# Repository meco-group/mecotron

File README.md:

# mecotron

This repository gathers software and hardware details on mobile platforms that were recently designed in support of an introductory control course.

Through dedicated assignments, students are guided to implement and validate all parts of the course on a setup, ranging from basic time-domain system identification, over root locus analysis and loop shaping PID design, to state feedback, state estimation and Kalman filtering.

The designed platforms are flexible, allowing for numerous extensions and variations; cheap, allowing for a large pool of setups from which the students can borrow platforms to take home; and of sufficient quality, allowing the students to get maximal insight in the course material.

The platforms are furthermore easy to set up and administer using the supporting material.

*These set-ups were presented at the demonstrator sessions at the 20th IFAC World Congress (Toulouse, 2017); see [the accompanying paper](https://www.sciencedirect.com/science/article/pii/S240589631732325X) and the video below.*

<p align="center">

</p>

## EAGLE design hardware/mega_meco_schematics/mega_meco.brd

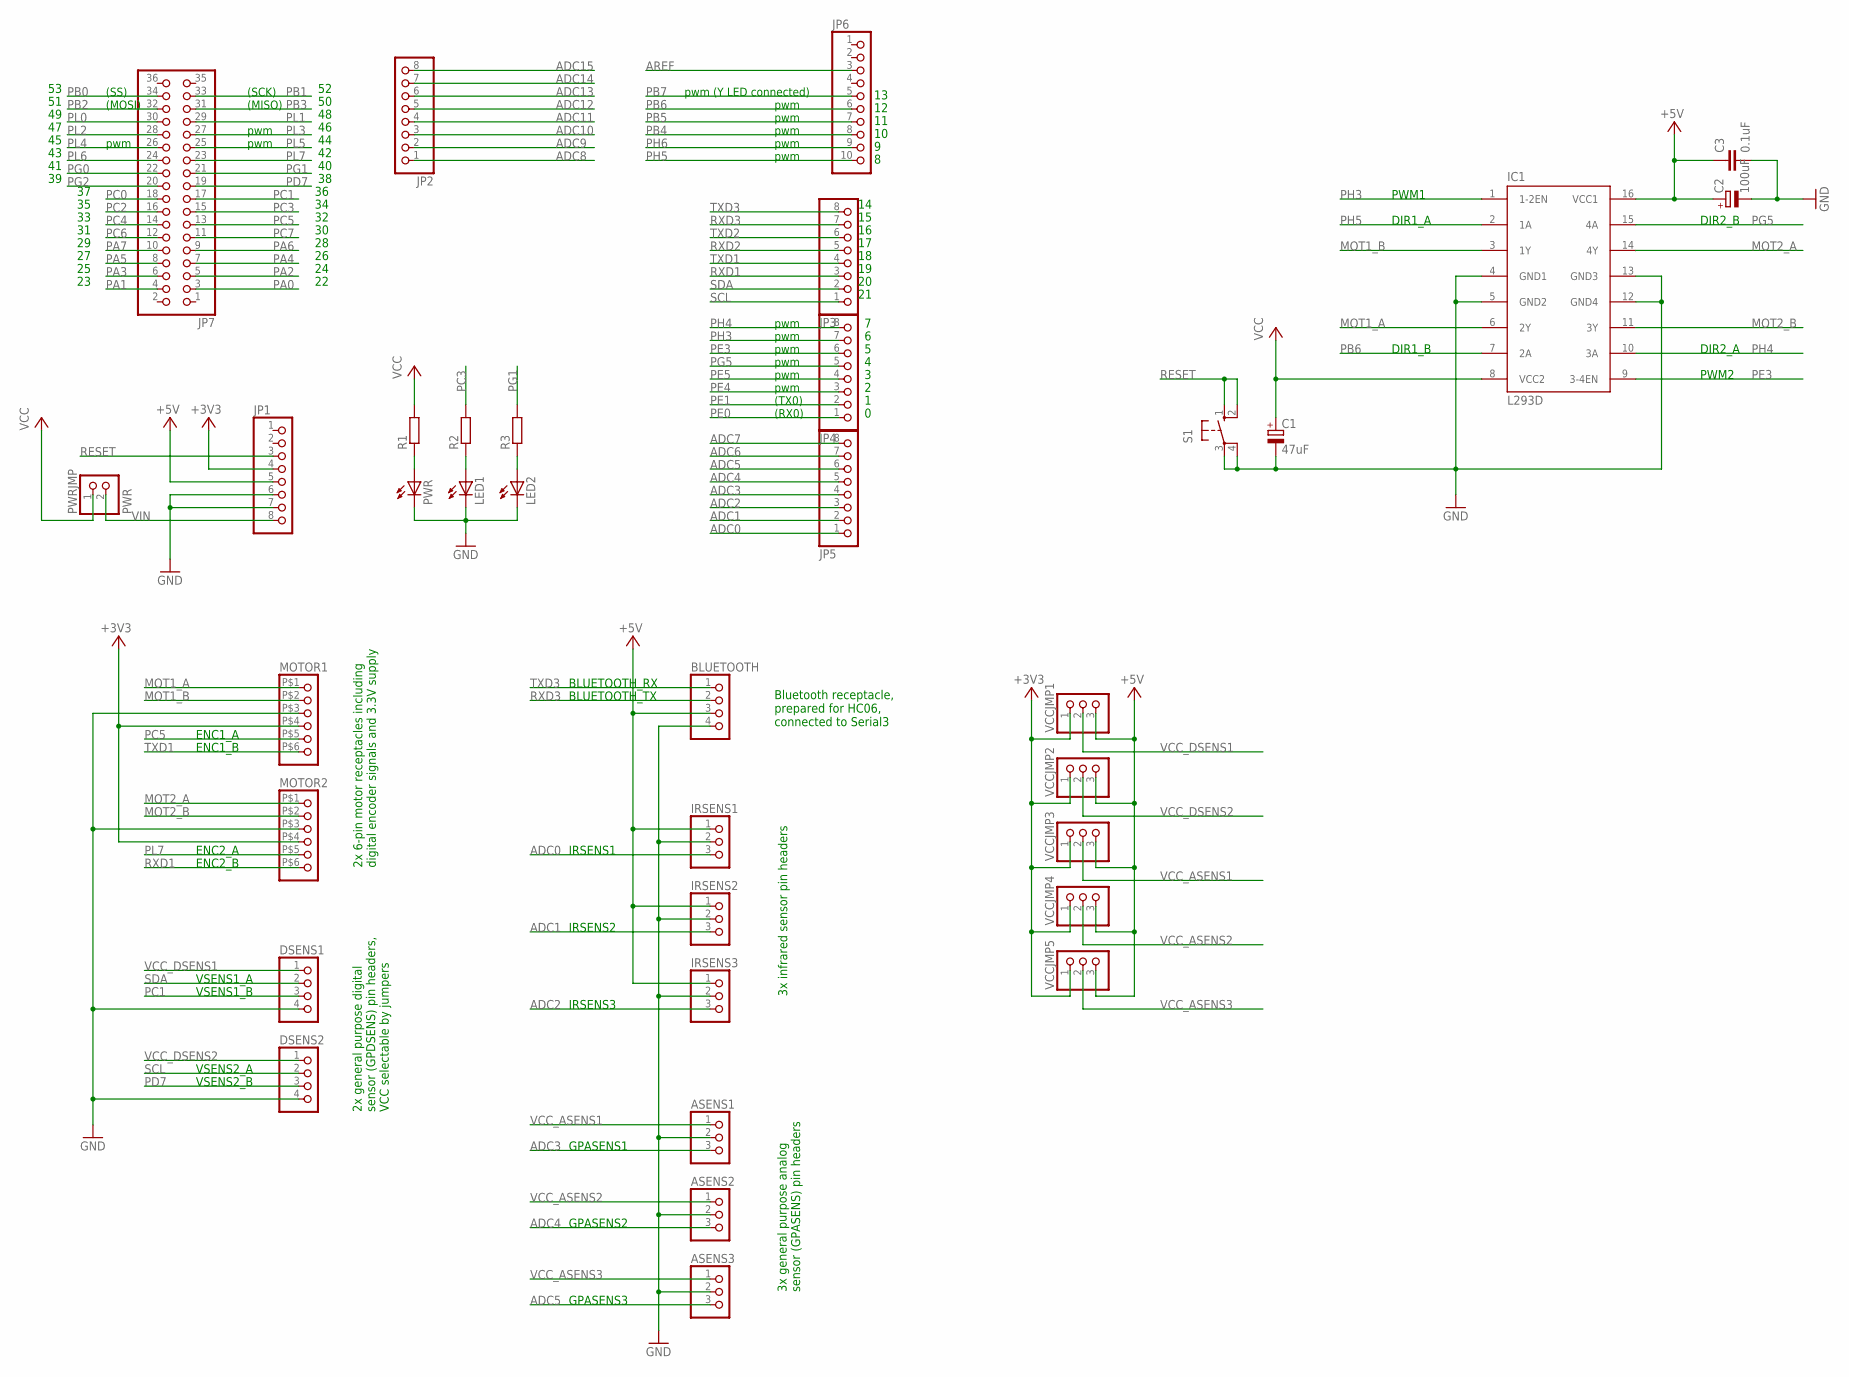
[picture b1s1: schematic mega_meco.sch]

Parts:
ASENS1, ASENS2, ASENS3: PINHD-1X3; 1X03
BLUETOOTH: PINHD-1X4; 1X04
C1: 47uF; E2-5
C2: 100uF; E2-5
C3: 0.1uF; C025-025X050
DSENS1, DSENS2: PINHD-1X4; 1X04
IC1: L293D; DIL16
IRSENS1, IRSENS2, IRSENS3: PINHD-1X3; 1X03
JP1, JP2, JP3, JP4, JP5: PINHD-1X8; 1X08
JP6: PINHD-1X10; 1X10
JP7: PINHD-2X18; 2X18
LED1, LED2: LED3MM
MOTOR1, MOTOR2: PINHD-1X6-2.5MM; 1X06-2.5MM
PWR: LED5MM
PWRJMP: PWR; 1X02
R1, R2, R3: R-EU_0204/5; 0204/5
S1: 10-XX; B3F-10XX
VCCJMP1, VCCJMP2, VCCJMP3, VCCJMP4, VCCJMP5: PINHD-1X3; 1X03

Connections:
+3V3: JP1.4, MOTOR1.P$4 (4), MOTOR2.P$4 (4), VCCJMP1.1, VCCJMP2.1, VCCJMP3.1, VCCJMP4.1, VCCJMP5.1
+5V: BLUETOOTH.3, C2.+, C3.1, IC1.16 (VCC1), IRSENS1.1, IRSENS2.1, IRSENS3.1, JP1.5, VCCJMP1.3, VCCJMP2.3, VCCJMP3.3, VCCJMP4.3, VCCJMP5.3
ADC0: IRSENS1.3, JP5.1
ADC1: IRSENS2.3, JP5.2
ADC2: IRSENS3.3, JP5.3
ADC3: ASENS1.3, JP5.4
ADC4: ASENS2.3, JP5.5
ADC5: ASENS3.3, JP5.6
ADC6: JP5.7
ADC7: JP5.8
ADC8: JP2.1
ADC9: JP2.2
ADC10: JP2.3
ADC11: JP2.4
ADC12: JP2.5
ADC13: JP2.6
ADC14: JP2.7
ADC15: JP2.8
AREF: JP6.3
GND: ASENS1.2, ASENS2.2, ASENS3.2, BLUETOOTH.4, C1.-, C2.-, C3.2, DSENS1.4, DSENS2.4, IC1.4 (GND1), IC1.5 (GND2), IC1.12 (GND4), IC1.13 (GND3), IRSENS1.2, IRSENS2.2, IRSENS3.2, JP1.6, JP1.7, LED1.K (C), LED2.K (C), MOTOR1.P$3 (3), MOTOR2.P$3 (3), PWR.K (C), S1.3, S1.4 (P1)
MOT1_A: IC1.6 (2Y), MOTOR1.P$1 (1)
MOT1_B: IC1.3 (1Y), MOTOR1.P$2 (2)
MOT2_A: IC1.14 (4Y), MOTOR2.P$1 (1)
MOT2_B: IC1.11 (3Y), MOTOR2.P$2 (2)
unnamed: PWR.A, R1.1
unnamed: LED1.A, R2.1
unnamed: LED2.A, R3.1
PA0: JP7.3
PA1: JP7.4
PA2: JP7.5
PA3: JP7.6
PA4: JP7.7
PA5: JP7.8
PA6: JP7.9
PA7: JP7.10
PB0: JP7.34
PB1: JP7.33
PB2: JP7.32
PB3: JP7.31
PB4: JP6.8
PB5: JP6.7
PB6: IC1.7 (2A), JP6.6
PB7: JP6.5
PC0: JP7.18
PC1: DSENS1.3, JP7.17
PC2: JP7.16
PC3: JP7.15, R2.2
PC4: JP7.14
PC5: JP7.13, MOTOR1.P$5 (5)
PC6: JP7.12
PC7: JP7.11
PD7: DSENS2.3, JP7.19
PE0: JP4.1
PE1: JP4.2
PE3: IC1.9 (3-4EN), JP4.6
PE4: JP4.3
PE5: JP4.4
PG0: JP7.22
PG1: JP7.21, R3.2
PG2: JP7.20
PG5: IC1.15 (4A), JP4.5
PH3: IC1.1 (1-2EN), JP4.7
PH4: IC1.10 (3A), JP4.8
PH5: IC1.2 (1A), JP6.10
PH6: JP6.9
PL0: JP7.30
PL1: JP7.29
PL2: JP7.28
PL3: JP7.27
PL4: JP7.26
PL5: JP7.25
PL6: JP7.24
PL7: JP7.23, MOTOR2.P$5 (5)
RESET: JP1.3, S1.1 (S), S1.2 (S1)
RXD1: JP3.3, MOTOR2.P$6 (6)
RXD2: JP3.5
RXD3: BLUETOOTH.2, JP3.7
SCL: DSENS2.2, JP3.1
SDA: DSENS1.2, JP3.2
TXD1: JP3.4, MOTOR1.P$6 (6)
TXD2: JP3.6
TXD3: BLUETOOTH.1, JP3.8
VCC: C1.+, IC1.8 (VCC2), PWRJMP.1, R1.2
VCC_ASENS1: ASENS1.1, VCCJMP3.2
VCC_ASENS2: ASENS2.1, VCCJMP4.2
VCC_ASENS3: ASENS3.1, VCCJMP5.2
VCC_DSENS1: DSENS1.1, VCCJMP1.2
VCC_DSENS2: DSENS2.1, VCCJMP2.2
VIN: JP1.8, PWRJMP.2

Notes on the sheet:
pwm (Y LED connected)
pwm
(TX0)
(RX0)
(SS)
(MOSI)
(SCK)
(MISO)
BLUETOOTH_RX
BLUETOOTH_TX
IRSENS1
IRSENS2
IRSENS3
GPASENS1
VSENS1_A
VSENS1_B
VSENS2_A
VSENS2_B
ENC2_A
ENC2_B
ENC1_A
ENC1_B
PWM1
DIR1_A
DIR1_B
DIR2_B
DIR2_A
PWM2
Bluetooth receptacle, prepared for HC06, connected to Serial3
3x infrared sensor pin headers
2x general purpose digital sensor (GPDSENS) pin headers, VCC selectable by jumpers
GPASENS2
GPASENS3
3x general purpose analog sensor (GPASENS) pin headers
2x 6-pin motor receptacles including digital encoder signals and 3.3V supply

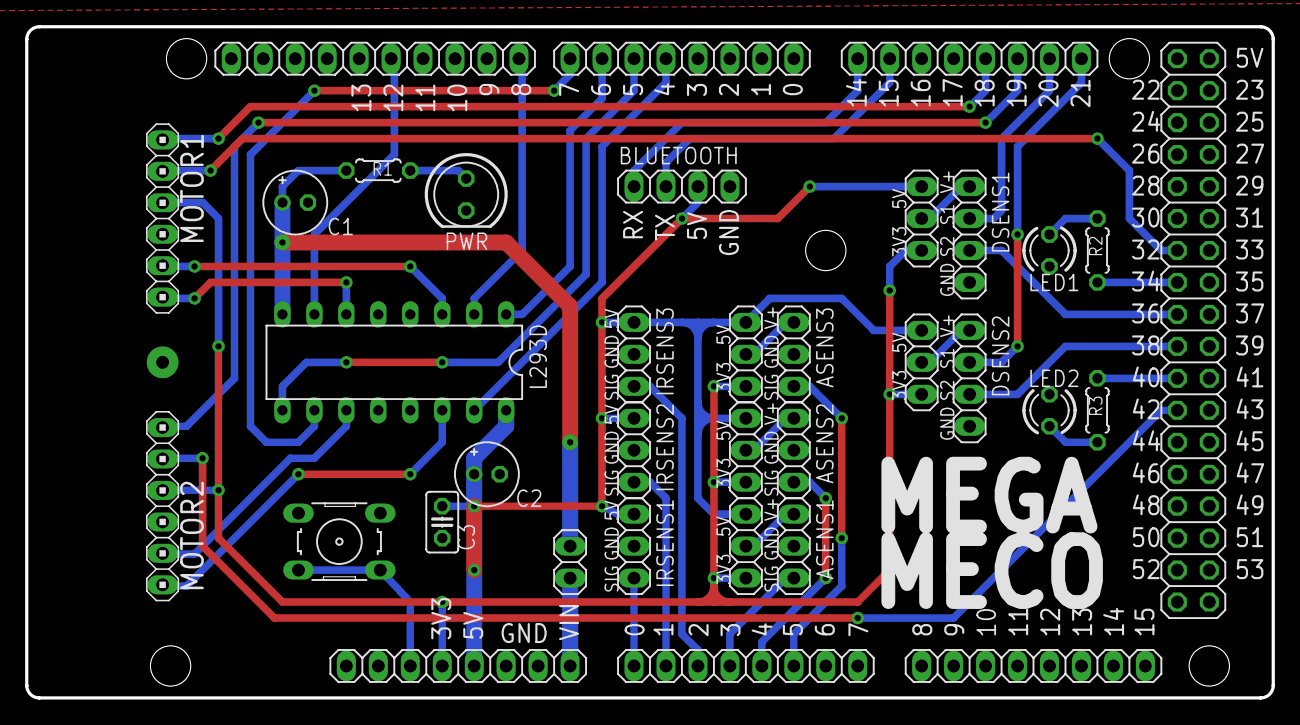
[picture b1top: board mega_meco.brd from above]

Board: 2 copper layers, 99.1 x 53.3 mm, 35 parts (0 on the bottom side), 42 nets.

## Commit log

2016-11-30 Add hardware details
2016-12-20 Added snapshot of MECO-CSI
2016-12-20 Added student files and unit test to the repo
2016-12-20 added some gitignore
2017-01-13 Pack Eagle files
2017-01-13 added assignments
2017-07-17 added ifac mecotron video to readme
2019-08-07 update to rev3. Part list still to be changed
2019-08-07 updated to rev3
2020-07-23 add link to paper
2020-07-23 add link to paper, bis
